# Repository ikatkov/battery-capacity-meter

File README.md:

# Assembly notes

Vref pin on Arduino Pro Mini breakout board is not on any pin, solder a wire to capacitor between 
pins 12 and 13. To the pin13 end.

Manufactured PCBs have a defect, bridge these tracks
see manufactured-pcb-defect.png

# 7 Segments text

Here is an example of which letters are possible

A,b,C,c,d,E,F,g,G,H,h,i,I,j,L,l,n,N,O,o,P,q,r,S,t,U,u,y

# Notes

* The final PCB layout that I ordered from https://jlcpcb.com/ is not great. This is my almost first attempt to really use two sides with a lot of vias. Maybe next time use the lower side for horizontal signal traces and the top side for vertical? 

* Maybe replace 2.5V ref to MCU with feeding the whole MCU from 2.5V ref, it eliminates the extra wire.

* Next time make use wider ribbon cable - use more LEDs on the front panel to indicate the current mode and state

* Update the firmware to include trickle charge, it's especially noticeable when charging to the 3.8V for storage, once 
charging power is removed - voltage drops.

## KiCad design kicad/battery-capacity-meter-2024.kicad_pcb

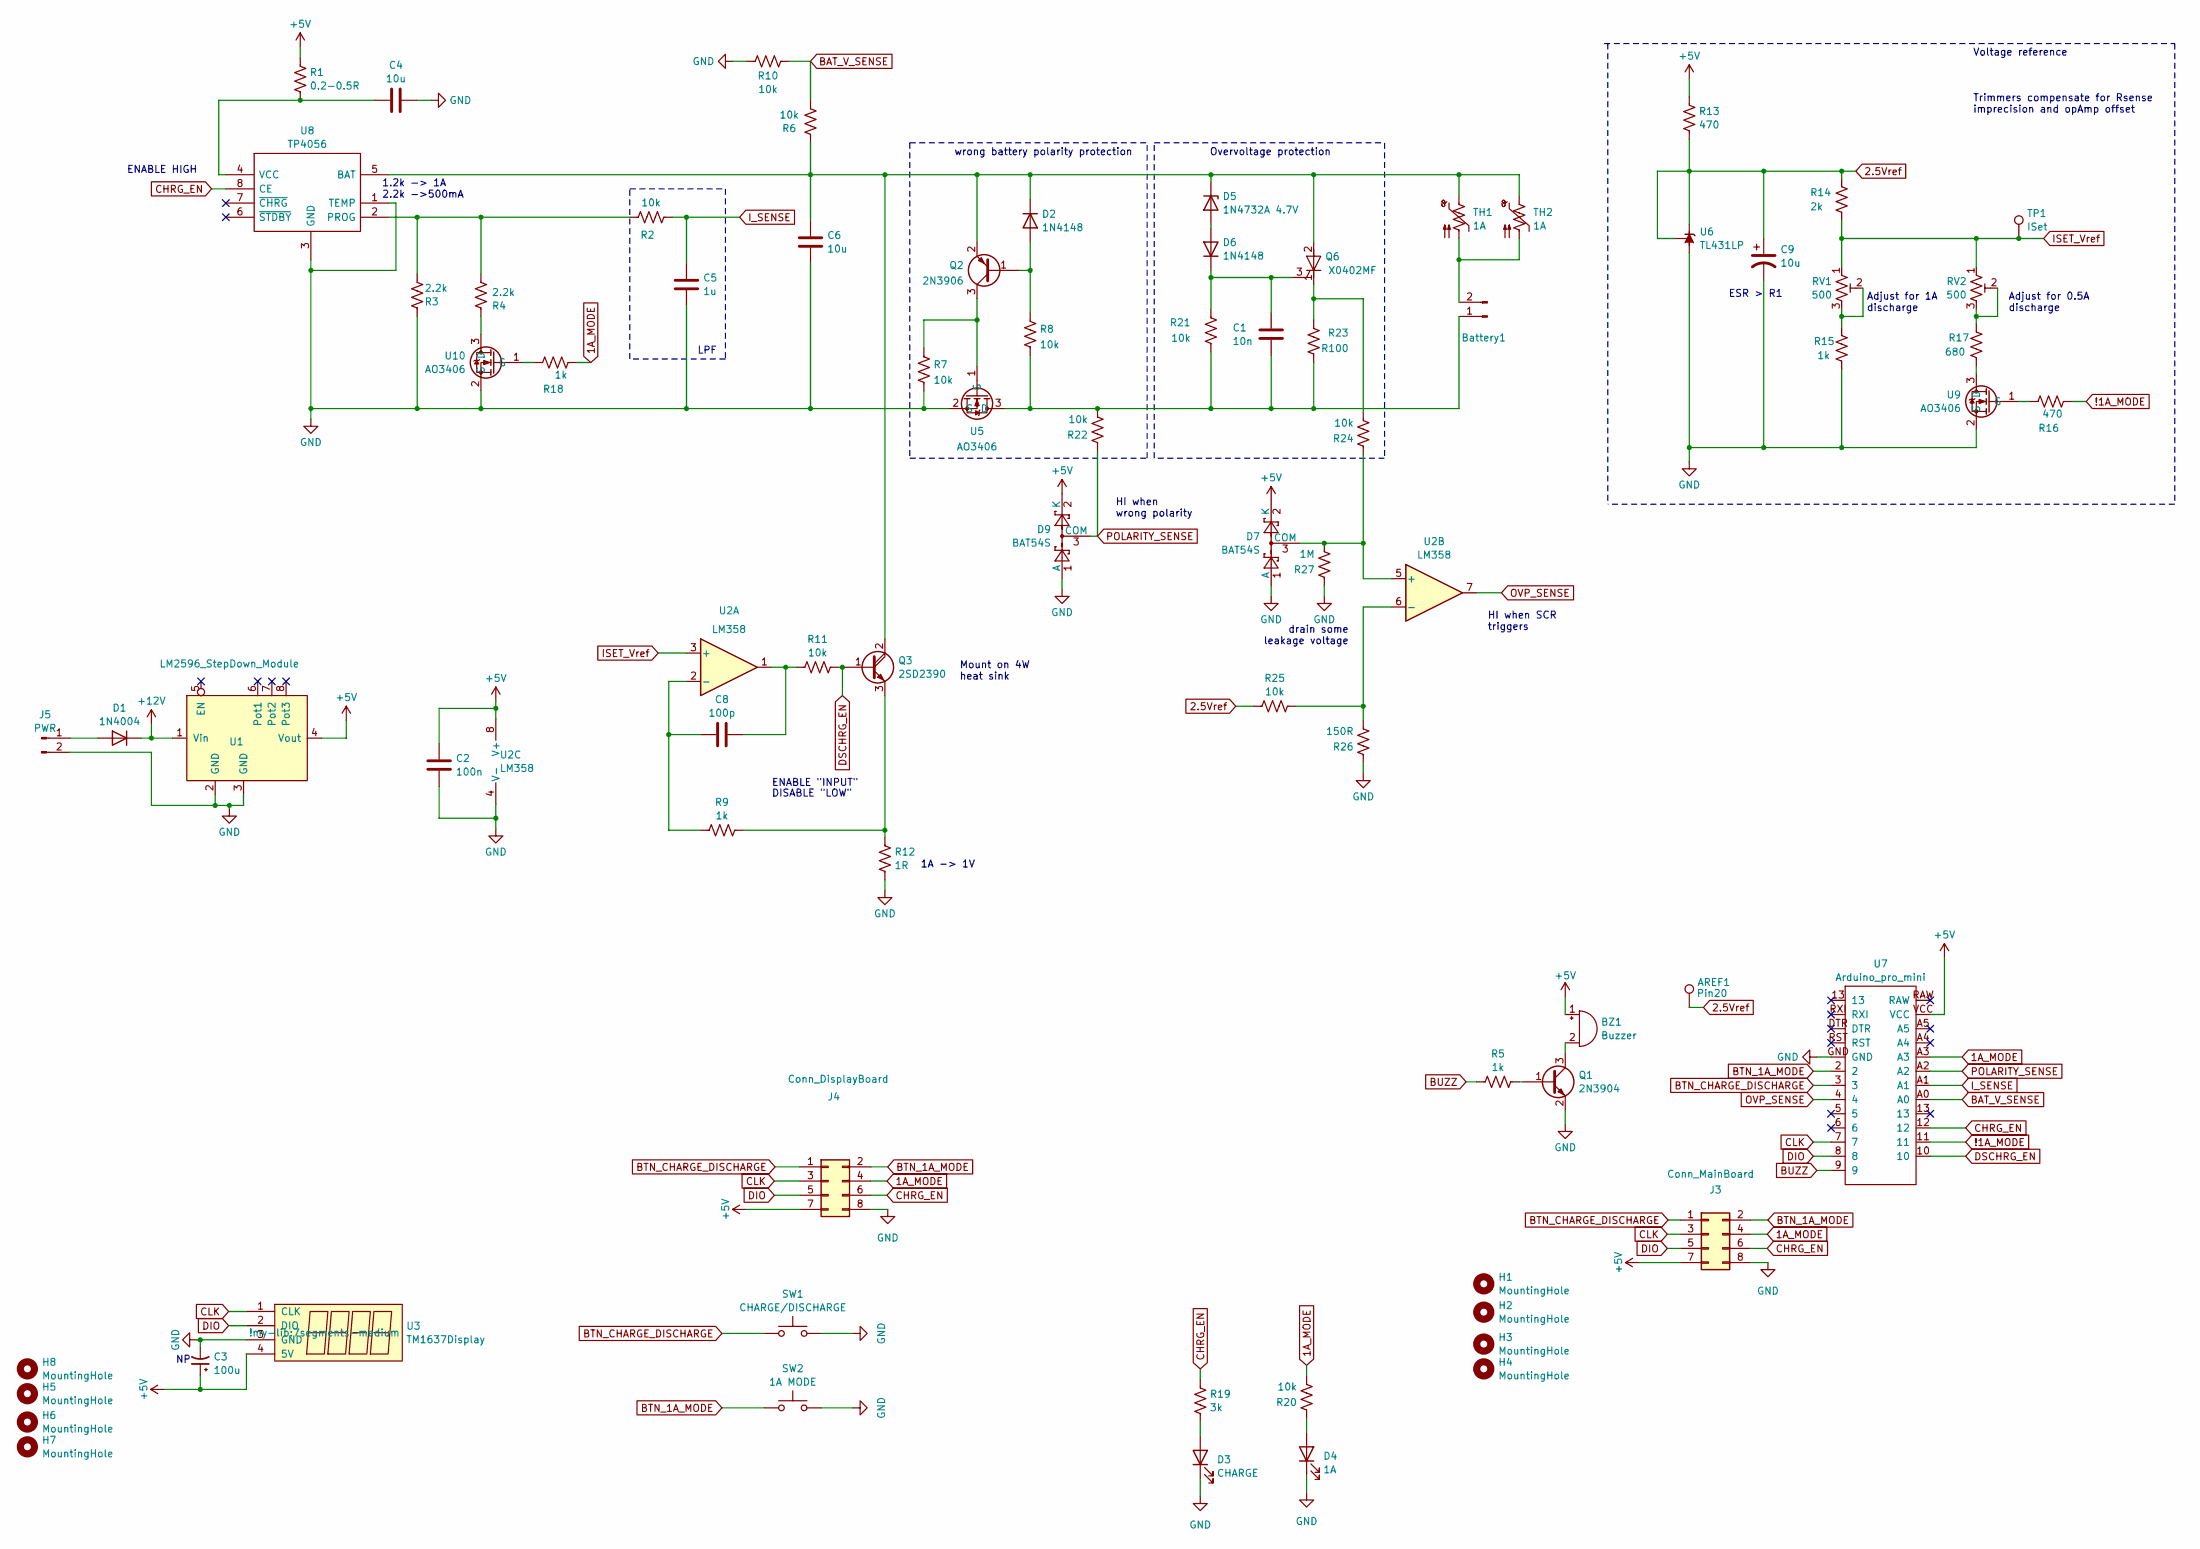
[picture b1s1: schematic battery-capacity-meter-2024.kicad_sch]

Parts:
AREF1: Pin20; SolderWire-0.5sqmm_1x01_D0.9mm_OD2.1mm
BZ1: Buzzer; Buzzer_12x9.5RM7.6
Battery1: Charger; JST_VH_B2P-VH-B_1x02_P3.96mm_Vertical
C1: 10n; C_1206_3216Metric
C2: 100n; C_1206_3216Metric
C3: 100u; CP_Radial_D8.0mm_P2.50mm
C4, C6: 10u; C_1206_3216Metric
C5: 1u; C_1206_3216Metric
C8: 100p; C_1206_3216Metric
C9: 10u; CP_Radial_D5.0mm_P2.50mm
D1: 1N4004; D_DO-41_SOD81_P10.16mm_Horizontal
D2, D6: 1N4148; D_MiniMELF
D3: CHARGE; LED_D5.0mm
D4: 1A; LED_D5.0mm
D5: 1N4732A 4.7V; D_MiniMELF
D7, D9: BAT54S; SOT-23
H1, H2, H3, H4: MountingHole; MountingHole_3.2mm_M3
H5, H6, H7, H8: MountingHole; MountingHole_2.2mm_M2
J3: Conn_MainBoard; IDC-Header_2x04_P2.54mm_Vertical
J4: Conn_DisplayBoard; IDC-Header_2x04_P2.54mm_Vertical_SMD
J5: PWR; JST_XH_B2B-XH-A_1x02_P2.50mm_Vertical
Q1: 2N3904; SOT-23
Q2: 2N3906; SOT-23
Q3: 2SD2390; TO-3P-3_Vertical
Q6: X0402MF; TO-220-3_Vertical
R1: 0.2-0.5R; R_Axial_DIN0614_L14.3mm_D5.7mm_P15.24mm_Horizontal
R2, R6, R7, R8, R10, R11, R20, R21, R22, R24, R25: 10k; R_0805_2012Metric
R3, R4: 2.2k; R_0805_2012Metric
R5, R9, R15, R18: 1k; R_0805_2012Metric
R12: 1R; R_Axial_DIN0614_L14.3mm_D5.7mm_P25.40mm_Horizontal
R13, R16: 470; R_0805_2012Metric
R14: 2k; R_0805_2012Metric
R17: 680; R_0805_2012Metric
R19: 3k; R_0805_2012Metric
R23: R100; R_2512_6332Metric
R26: 150R; R_0805_2012Metric
R27: 1M; R_0805_2012Metric
RV1, RV2: 500; Potentiometer_Runtron_RM-065_Vertical
SW1: CHARGE/DISCHARGE; SW_PUSH_6mm
SW2: 1A MODE; SW_PUSH_6mm
TH1, TH2: 1A; PTC_1A_radial
TP1: ISet; SolderWire-0.5sqmm_1x01_D0.9mm_OD2.1mm
U1: LM2596_StepDown_Module; LM2596_StepDown_pot
U2: LM358; SO-8_3.9x4.9mm_P1.27mm
U3: TM1637Display; 7segments-medium
U5, U9, U10: AO3406; SOT-23
U6: TL431LP; TO-92_Wide
U7: Arduino_pro_mini; ARDUINO_PRO_MINI_NO_PRG_HEADER
U8: TP4056; SO-8_3.9x4.9mm_P1.27mm; Manufacturer_Part_Number TP4056

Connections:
1A_MODE: J3.4, J4.4, R18.2, R20.1, U7.A3
2.5Vref: AREF1.1, C9.1, R13.2, R14.1, R25.1, U6.1 (REF), U6.3 (K)
!1A_MODE: R16.2, U7.11
+5V: BZ1.1 (-), C2.1, C3.1, D7.2 (K), D9.2 (K), J3.7, J4.7, R1.1, R13.1, U1.4 (Vout), U2.8 (V+), U3.4 (5V), U7.VCC
+12V: D1.1 (K), U1.1 (Vin)
BAT_V_SENSE: R6.2, R10.1, U7.A0
BTN_1A_MODE: J3.2, J4.2, SW2.1, U7.2
BTN_CHARGE_DISCHARGE: J3.1, J4.1, SW1.1, U7.3
BUZZ: R5.1, U7.9
CHRG_EN: J3.6, J4.6, R19.1, U7.12, U8.8 (CE)
CLK: J3.3, J4.3, U3.1 (CLK), U7.7
DIO: J3.5, J4.5, U3.2 (DIO), U7.8
DSCHRG_EN: Q3.1 (B), R11.2, U7.10
GND: C2.2, C3.2, C4.2, C5.2, C6.2, C9.2, D3.1 (K), D4.1 (K), D7.1 (A), D9.1 (A), J3.8, J4.8, J5.2, Q1.2 (E), R3.2, R7.1, R10.2, R12.1, R15.2, R26.2, R27.2, SW1.2, SW2.2, U1.2 (GND), U1.3 (GND), U2.4 (V-), U3.3 (GND), U5.2 (S), U6.2 (A), U7.GND, U8.1 (TEMP), U8.3 (GND), U9.2 (S), U10.2 (S)
ISET_Vref: R14.2, RV1.1, RV2.1, TP1.1, U2.3 (+)
I_SENSE: C5.1, R2.2, U7.A1
unnamed: BZ1.2 (+), Q1.3 (C)
unnamed: Battery1.1, C1.2, R8.1, R21.2, R22.1, R23.2, U5.3 (D)
unnamed: Battery1.2, TH1.2, TH2.2
unnamed: C8.2, R11.1, U2.1
unnamed: D1.2 (A), J5.1
unnamed: D2.2 (A), Q2.1 (B), R8.2
unnamed: C6.1, D2.1 (K), D5.1 (K), Q2.2 (E), Q3.2 (C), Q6.2 (A), Q6.4 (A), R6.1, TH1.1, TH2.1, U8.5 (BAT)
unnamed: D3.2 (A), R19.2
unnamed: D4.2 (A), R20.2
unnamed: D5.2 (A), D6.2 (A)
unnamed: C1.1, D6.1 (K), Q6.3 (G), R21.1
unnamed: D7.3 (COM), R24.2, R27.1, U2.5 (+)
unnamed: Q1.1 (B), R5.2
unnamed: Q2.3 (C), R7.2, U5.1 (G)
unnamed: Q3.3 (E), R9.2, R12.2
unnamed: Q6.1 (K), R23.1, R24.1
unnamed: R15.1, RV1.2, RV1.3
unnamed: R17.1, RV2.2, RV2.3
unnamed: C8.1, R9.1, U2.2 (-)
unnamed: R25.2, R26.1, U2.6 (-)
unnamed: R2.1, R3.1, R4.1, U8.2 (PROG)
unnamed: C4.1, R1.2, U8.4 (VCC)
unnamed: R17.2, U9.3 (D)
unnamed: R16.1, U9.1 (G)
unnamed: R4.2, U10.3 (D)
unnamed: R18.1, U10.1 (G)
OVP_SENSE: U2.7, U7.4
POLARITY_SENSE: D9.3 (COM), R22.2, U7.A2

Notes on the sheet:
ESR > R1
HI when SCR triggers
Voltage reference Trimmers compensate for Rsense imprecision and opAmp offset
HI when wrong polarity
Overvoltage protection
Adjust for 0.5A discharge
Mount on 4W heat sink
LPF
ENABLE "INPUT"
DISABLE "LOW"
Adjust for 1A discharge
ENABLE HIGH
drain some leakage voltage
1A -> 1V
1.2k -> 1A 2.2k ->500mA
wrong battery polarity protection

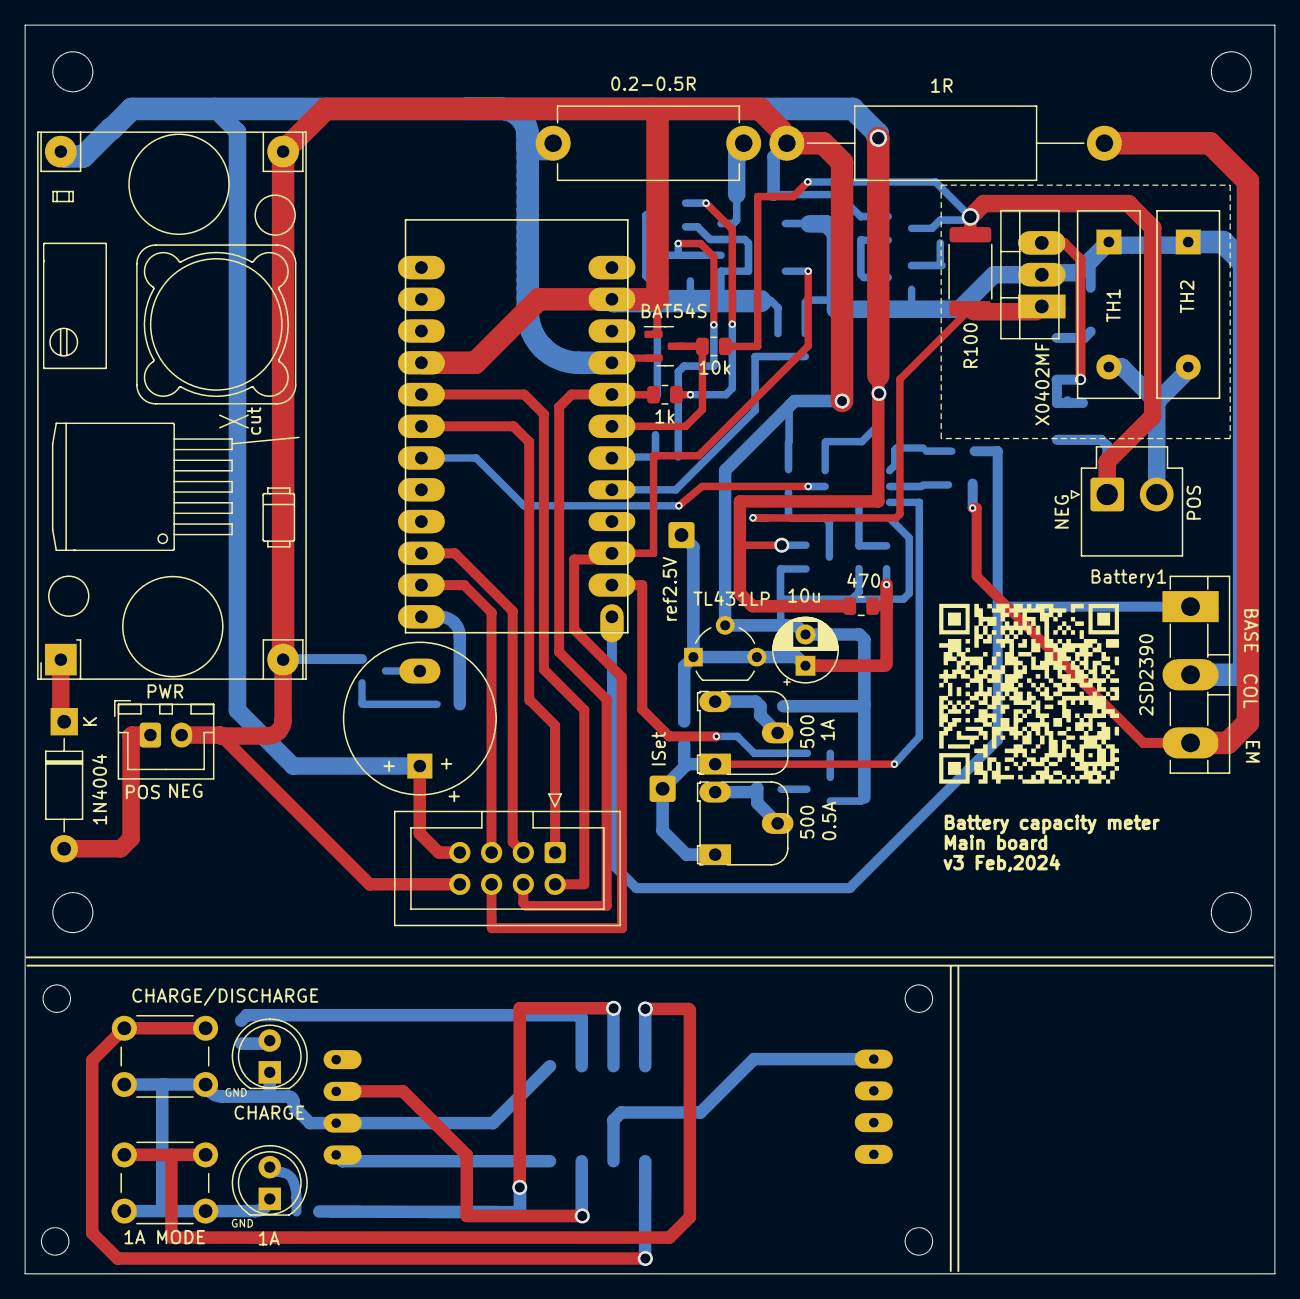
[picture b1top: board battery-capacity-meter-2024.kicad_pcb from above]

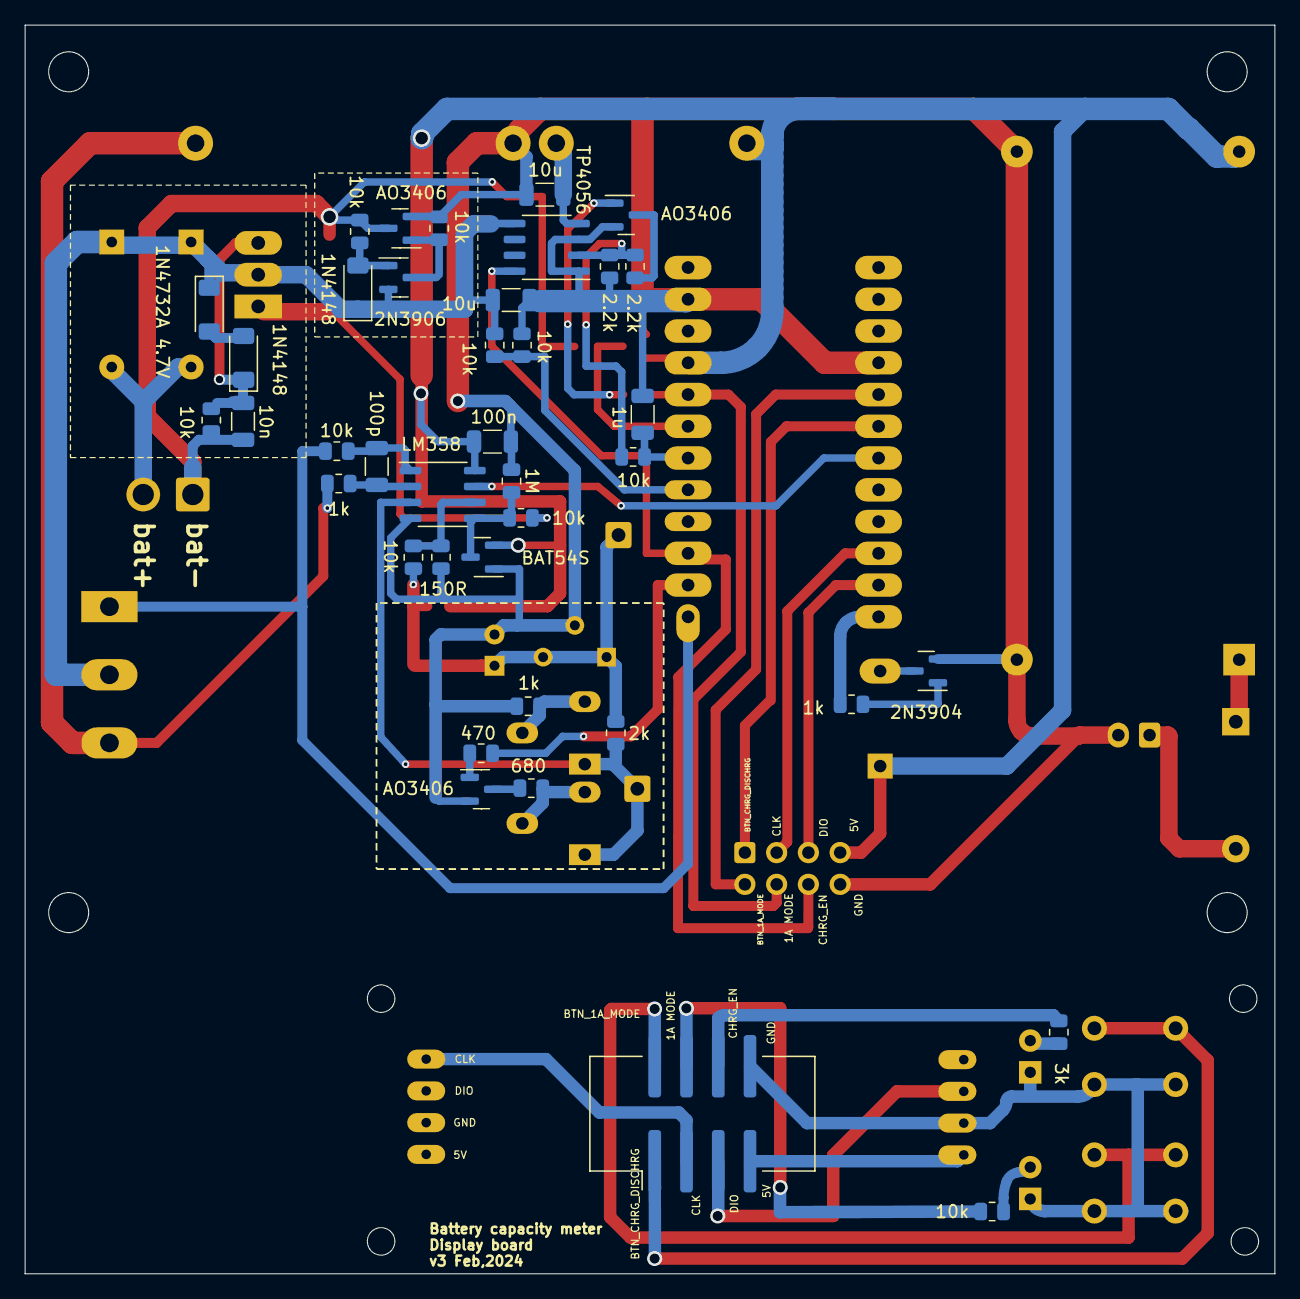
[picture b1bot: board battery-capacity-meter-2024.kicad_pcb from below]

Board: 2 copper layers, 100.0 x 99.9 mm, 76 parts (39 on the bottom side), 44 nets.

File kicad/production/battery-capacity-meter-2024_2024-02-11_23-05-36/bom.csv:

Designator,Footprint,Quantity,Value,LCSC Part #
AREF1,SolderWire-0.5sqmm_1x01_D0.9mm_OD2.1mm,1,Pin20,
BZ1,Buzzer_12x9.5RM7.6,1,Buzzer,
Battery1,JST_VH_B2P-VH-B_1x02_P3.96mm_Vertical,1,Charger,
C1,1206,1,10n,
C2,1206,1,100n,
"C4, C6",1206,2,10u,
C5,1206,1,1u,
C8,1206,1,100p,
C9,CP_Radial_D5.0mm_P2.50mm,1,10u,
D1,D_DO-41_SOD81_P10.16mm_Horizontal,1,1N4004,
"D2, D6",D_MiniMELF,2,1N4148,
D3,LED_D5.0mm,1,CHARGE,
D4,LED_D5.0mm,1,1A,
D5,D_MiniMELF,1,1N4732A 4.7V,
"D7, D9",SOT-23,2,BAT54S,
"H1, H2, H3, H4",MountingHole_3.2mm_M3,4,MountingHole,
"H5, H6, H7, H8",MountingHole_2.2mm_M2,4,MountingHole,
J3,IDC-Header_2x04_P2.54mm_Vertical,1,Conn_MainBoard,
J4,IDC-Header_2x04_P2.54mm_Vertical_SMD,1,Conn_DisplayBoard,
J5,JST_XH_B2B-XH-A_1x02_P2.50mm_Vertical,1,PWR,
Q1,SOT-23,1,2N3904,
Q2,SOT-23,1,2N3906,
Q3,TO-3P-3_Vertical,1,2SD2390,
Q6,TO-220-3_Vertical,1,X0402MF,
R1,R_Axial_DIN0614_L14.3mm_D5.7mm_P15.24mm_Horizontal,1,0.2-0.5R,
"R10, R11, R2, R20, R21, R22, R24, R25, R6, R7, R8",0805,11,10k,
R12,R_Axial_DIN0614_L14.3mm_D5.7mm_P25.40mm_Horizontal,1,1R,
"R13, R16",0805,2,470,
R14,0805,1,2k,
"R15, R18, R5, R9",0805,4,1k,
R17,0805,1,680,
R19,0805,1,3k,
R23,2512,1,R100,
R26,0805,1,150R,
R27,0805,1,1M,
"R3, R4",0805,2,2.2k,
"RV1, RV2",Potentiometer_Runtron_RM-065_Vertical,2,500,
SW1,SW_PUSH_6mm,1,CHARGE/DISCHARGE,
SW2,SW_PUSH_6mm,1,1A MODE,
"TH1, TH2",PTC_1A_radial,2,1A,
TP1,SolderWire-0.5sqmm_1x01_D0.9mm_OD2.1mm,1,ISet,
U1,LM2596_StepDown_pot,1,LM2596_StepDown_Module,
"U10, U5, U9",SOT-23,3,AO3406,
U2,SO-8_3.9x4.9mm_P1.27mm,1,LM358,
U3,7segments-medium,1,TM1637Display,
U6,TO-92_Wide,1,TL431LP,
U7,ARDUINO_PRO_MINI_NO_PRG_HEADER,1,Arduino_pro_mini,
U8,SO-8_3.9x4.9mm_P1.27mm,1,TP4056,

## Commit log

2024-02-04 hardware-ok. firware barelly workin
2024-02-05 working v1
2024-02-05 removed backup
2024-02-06 add ovp
2024-02-07 Ignore battery voltage that is too low
2024-02-11 add overvoltage protection in hardware and cycle modes in firmware
2024-02-12 before tracks reset
2024-02-12 ready two layers
2024-02-12 jlc-pcb order
2024-02-12 add back 4.150V as stop charge threshold
2024-02-12 typo fix
2024-02-13 overflow bug fix
2024-02-13 set storage voltage to 3.8V; new mode - storage only
2024-02-13 change logging message
2024-02-13 bug fixes
2024-02-13 bugfix
2024-02-19 Readme update
2024-07-28 moved code around
2024-07-28 fix missing pcb track
2024-07-31 fix state when battery was never connected
